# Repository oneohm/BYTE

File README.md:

# The BYTE
Full design package for the BYTE hands free interface

Details are available on the Hackaday project page:`
https://hackaday.io/project/171778-the-byte

## Repository Architecture

This repository is divided by 4 main folders:

- Docs: You'll find here our consult documents, and documentation of the project.
- Firmware: You'll find here everything you need to build the firmware and in case of needed, modify it.
- Hardware: You'll find here the KiCad projects with theirs libraries so the design is fully portable.
- Mechanical: You''ll find here all the FreeCad files to print/modify/understand the mechanics of the device.

You will find more information on each README in each folder, in order to keep this readme short.

# Previous Versions

It's important to note that this repository is under development, if your interested on one "The Byte" device already working, you should jump to the [Realese section](https://github.com/oneohm/BYTE/releases) of this repository to get the V1.0

## Version 1.0 

The version 1.0 has this architecture based on Seeeduino XIAO and all the connection is done by USB.

## License Info:

Firmware is licensed under the GNU General Public License v3.0

Hardware design is licensed under <br />This work is licensed under a <a rel="license" href="http://creativecommons.org/licenses/by-nc-sa/4.0/">Creative Commons Attribution-NonCommercial-ShareAlike 4.0 International License</a>.

Once the design is finalized the hardware will recieve a more permissive license.

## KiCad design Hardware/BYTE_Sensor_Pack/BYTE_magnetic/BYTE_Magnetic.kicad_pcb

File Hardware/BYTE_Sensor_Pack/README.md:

# The BYTE
Full design package for the BYTE hands free interface

Details are available on the Hackaday project page:`
https://hackaday.io/project/171778-the-byte

# Sensor Pack 

 You'll find here the KiCad projects for the different sensor packs.

- BYTE_Sensors.pretty: Library folder for all the KiCad footprints used in the sensor pack development.

- BYTE_FSR: First sensor pack used, only FSR for X/Y axis.

- BYTE_Bite: First sensor pack used, only FSR also for the bite.

- BYTE_Capacitive: Sensor intended to be used as capacitive feedback for FSR shift error.

- ...more to come.

## License Info:

Firmware is licensed under the GNU General Public License v3.0

Hardware design is licensed under <br />This work is licensed under a <a rel="license" href="http://creativecommons.org/licenses/by-nc-sa/4.0/">Creative Commons Attribution-NonCommercial-ShareAlike 4.0 International License</a>.

Once the design is finalized the hardware will recieve a more permissive license.

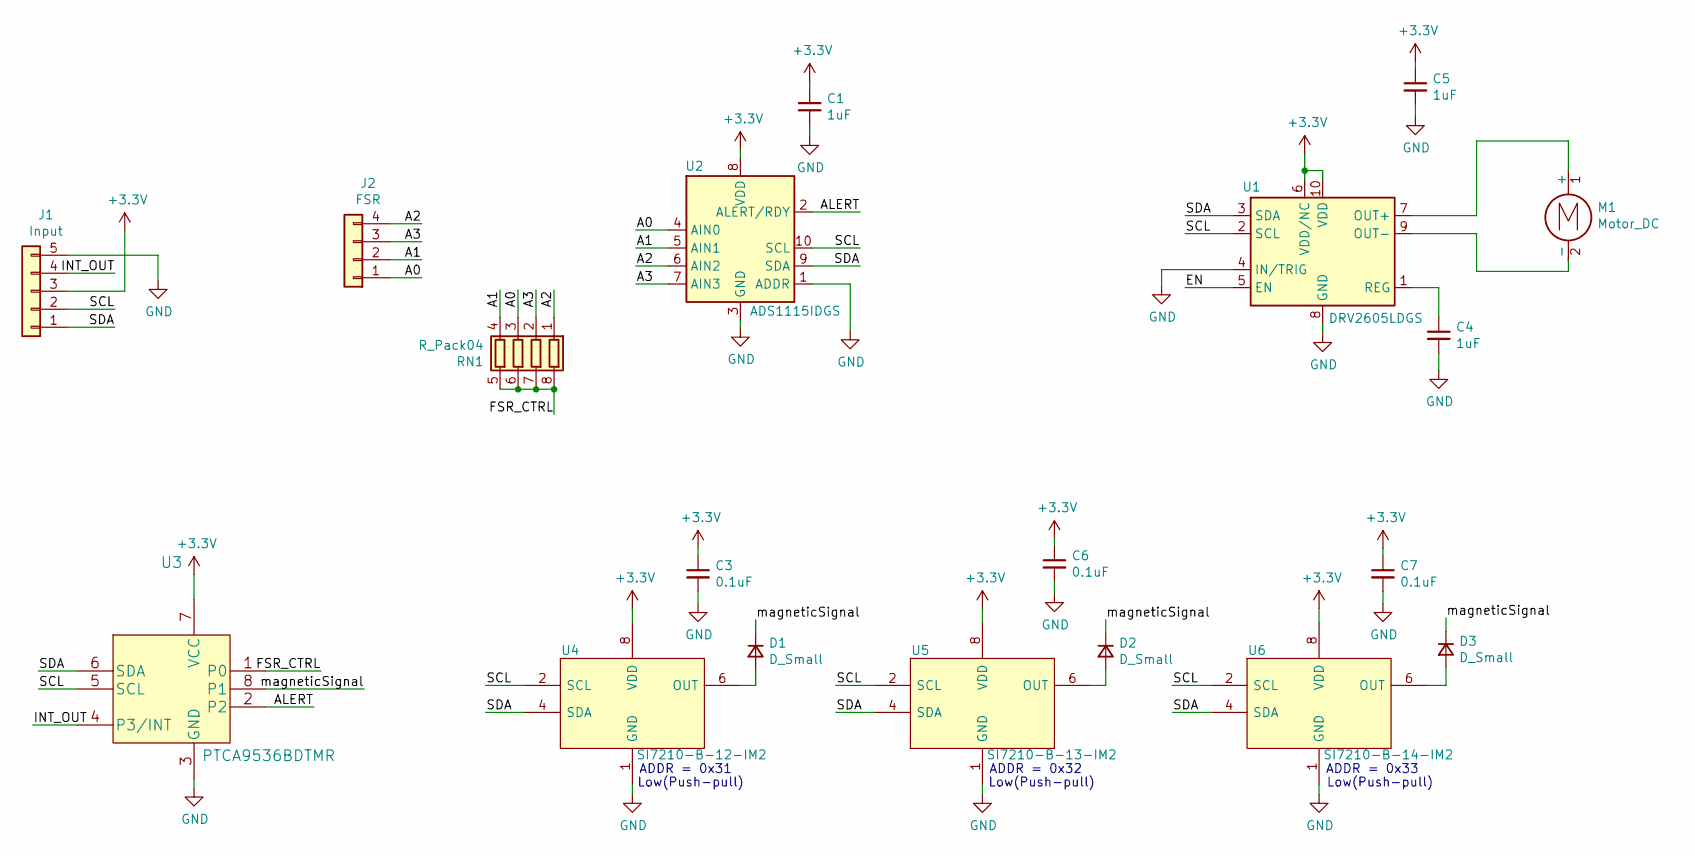
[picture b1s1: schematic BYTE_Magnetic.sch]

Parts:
C1, C4, C5: 1uF; C_0603_1608Metric
C3, C6, C7: 0.1uF; C_0603_1608Metric
D1, D2, D3: D_Small; D_0603_1608Metric
J1: Input; Flex_Connector
J2: FSR
M1: Motor_DC; VLV041235L
RN1: R_Pack04; R_Array_Convex_4x0603
U1: DRV2605LDGS; VSSOP-10_3x3mm_P0.5mm
U2: ADS1115IDGS; TSSOP-10_3x3mm_P0.5mm
U3: PTCA9536BDTMR; PTCA9416DTMR
U4: SI7210-B-12-IM2; SON40P140X160X40-8N-D
U5: SI7210-B-13-IM2; SON40P140X160X40-8N-D
U6: SI7210-B-14-IM2; SON40P140X160X40-8N-D

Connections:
+3V3: C1.1, C3.1, C5.1, C6.1, C7.1, J1.3, U1.6 (VDD/NC), U1.10 (VDD), U2.8 (VDD), U3.7 (VCC), U4.8 (VDD), U5.8 (VDD), U6.8 (VDD)
/A0: J2.1, RN1.3 (R3.1), U2.4 (AIN0)
/A1: J2.2, RN1.4 (R4.1), U2.5 (AIN1)
/A2: J2.4, RN1.1 (R1.1), U2.6 (AIN2)
/A3: J2.3, RN1.2 (R2.1), U2.7 (AIN3)
/ALERT: U2.2 (ALERT/RDY), U3.2
/EN: U1.5 (EN)
/FSR_CTRL: RN1.5 (R4.2), RN1.6 (R3.2), RN1.7 (R2.2), RN1.8 (R1.2), U3.1 (P0)
/INT_OUT: J1.4, U3.4 (P3/INT)
/SCL: J1.2, U1.2 (SCL), U2.10 (SCL), U3.5 (SCL), U4.2 (SCL), U5.2 (SCL), U6.2 (SCL)
/SDA: J1.1, U1.3 (SDA), U2.9 (SDA), U3.6 (SDA), U4.4 (SDA), U5.4 (SDA), U6.4 (SDA)
/magneticSignal: D1.1 (K), D2.1 (K), D3.1 (K), U3.8 (P1)
GND: C1.2, C3.2, C4.2, C5.2, C6.2, C7.2, J1.5, U1.4 (IN/TRIG), U1.8 (GND), U2.1 (ADDR), U2.3 (GND), U3.3 (GND), U4.1 (GND), U4.5 (GND), U5.1 (GND), U5.5 (GND), U6.1 (GND), U6.5 (GND)
unnamed: C4.1, U1.1 (REG)
unnamed: D1.2 (A), U4.6 (OUT)
unnamed: D2.2 (A), U5.6 (OUT)
unnamed: D3.2 (A), U6.6 (OUT)
unnamed: M1.1 (+), U1.7 (OUT+)
unnamed: M1.2 (-), U1.9 (OUT-)

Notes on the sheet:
ADDR = 0x31
ADDR = 0x32
ADDR = 0x33
Low(Push-pull)

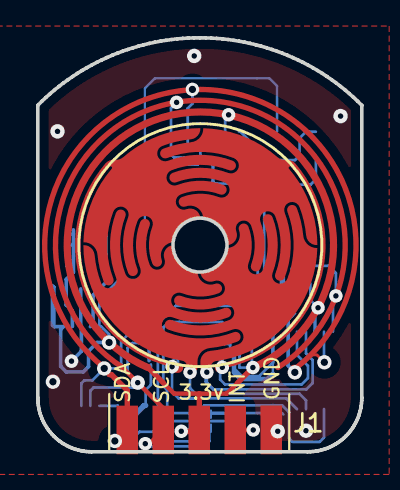
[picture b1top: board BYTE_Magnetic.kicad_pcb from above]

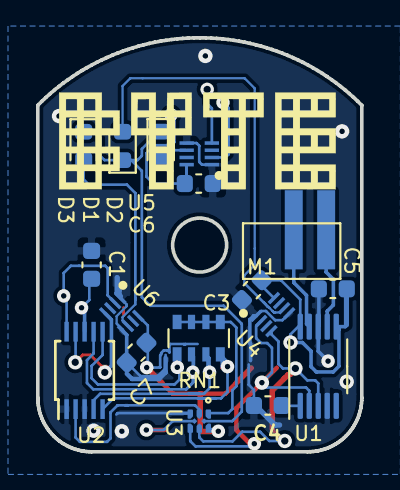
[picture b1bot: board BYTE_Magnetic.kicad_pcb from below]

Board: 2 copper layers, 18.0 x 23.0 mm, 19 parts (17 on the bottom side), 18 nets.

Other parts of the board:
Ref**: Val**; Logo

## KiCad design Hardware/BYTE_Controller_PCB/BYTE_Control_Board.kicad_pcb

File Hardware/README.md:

# The BYTE
Full design package for the BYTE hands free interface

Details are available on the Hackaday project page:`
https://hackaday.io/project/171778-the-byte

# Hardware 

 You'll find here the KiCad projects with theirs libraries so the design is fully portable among other folders with more hardware related information.

- BYTE_Bill_Of_Materials: Bill of materials of the electronics
- BYTE_Controller_PCB:  KiCad project for the main controller.
- BYTE_Full_Schematics: Full schematic in PDF for easy reading without KiCad.
- BYTE_Sensor_Artwork: All SVG files used to convert shapes from FreeCad to KiCad
- BYTE_Sensors_PCB: KiCad projects for the different sensor packs. 

You will find more information on each README in each folder, in order to keep this readme short.

## License Info:

Firmware is licensed under the GNU General Public License v3.0

Hardware design is licensed under <br />This work is licensed under a <a rel="license" href="http://creativecommons.org/licenses/by-nc-sa/4.0/">Creative Commons Attribution-NonCommercial-ShareAlike 4.0 International License</a>.

Once the design is finalized the hardware will recieve a more permissive license.

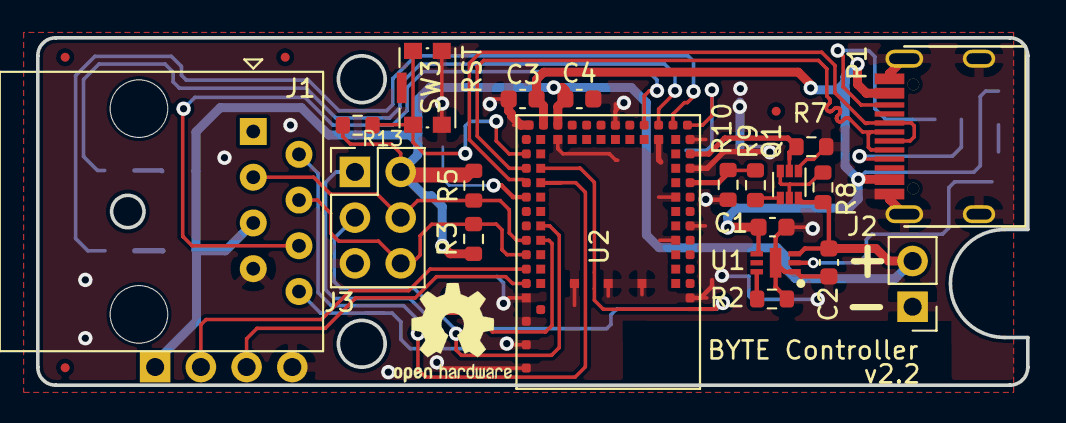
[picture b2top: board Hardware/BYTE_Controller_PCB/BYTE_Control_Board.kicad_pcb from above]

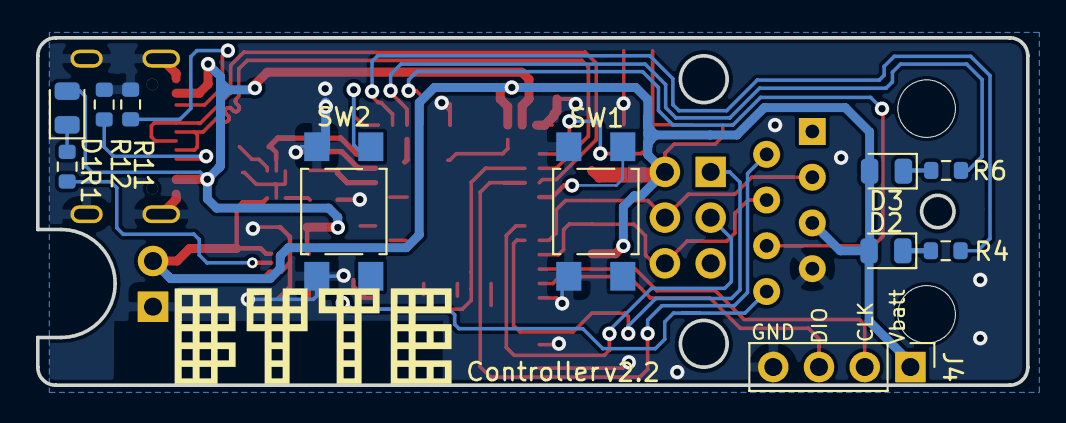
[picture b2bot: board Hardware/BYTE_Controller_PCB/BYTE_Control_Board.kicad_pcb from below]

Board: 2 copper layers, 55.0 x 19.3 mm, 32 parts (11 on the bottom side), 30 nets.

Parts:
C1, C2, C3: 4.7uF; C_0603_1608Metric
C4: 100nF; C_0603_1608Metric
D1, D2, D3: RED; LED_0805_2012Metric
J1: 8P8C_Shielded; RJ45_Amphenol_54602-x08_Horizontal
J2: Battery; PinHeader_1x02_P2.54mm_Vertical
J3: Expansion; PinHeader_2x03_P2.54mm_Vertical
J4: SWD; PinHeader_1x04_P2.54mm_Vertical
P1: USB_C_Plug_USB2.0; C393939
Q1: DMC2400UV; SOT-563
R1, R2, R3, R4, R5, R6, R7, R8, R9, R10: 2K; R_0603_1608Metric
R11: 5.1K; R_0603_1608Metric
R12: 5.1k; R_0603_1608Metric
R13: 10K; R_0603_1608Metric
Ref**: Val**; Logo
SW1, SW2: GPIO; SW_SPST_TL3305A
SW3: RST; SW_Push_1P1T-SH_NO_CK_KMR2xxG
U1: MCP73830T-2AAI_MYY; 2x2TDFN
U2: BL653; BL653_v5

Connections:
+BATT: C2.1, C4.1, D2.2, D3.2, J1.5, J2.2, J3.2, J4.1, Q1.6, R3.2, R5.2, R8.2, R13.2, U1.3, U2.25
/BATT_LVL: R9.1, R10.2, U2.49
/BATT_LVL_EN: Q1.2, R7.2, U2.45
/BYTE_SENSOR_1: J1.2, U2.16
/BYTE_SENSOR_2: J1.8, U2.18
/CC1: P1.A5, R12.1
/CC2: P1.B5, R11.2
/D+: P1.A6, U2.15
/D-: P1.A7, U2.17
/RST: R13.1, SW3.1, U2.19
/SCL: J1.4, J3.6, R3.1, U2.5
/SDA: J1.3, J3.4, R5.1, U2.7
/SIO_0: SW2.1, U2.42
/SIO_1: R4.1, U2.41
/SIO_5: R6.1, U2.39
/SIO_20: SW1.1, U2.13
/SIO_24: J3.3, U2.10
/SIO_25: J3.1, U2.8
/STAT: R1.1, U1.2
/SWCLK: J4.2, U2.3
/SWDIO: J4.3, U2.1
/Sensor_INT: J1.6, U2.37
GND: C1.2, C2.2, C3.2, C4.2, J1.7, J2.1, J3.5, J4.4, P1.A1, P1.S1, Q1.1, R2.1, R7.1, R10.1, R11.1, R12.2, SW1.2, SW2.2, SW3.2, U1.1, U1.7, U2.0, U2.23, U2.26, U2.33, U2.40, U2.43, U2.47, U2.52, U2.55, U2.58, U2.65, U2.66, U2.67, U2.68, U2.69, U2.70, U2.71
unnamed: D1.1, R1.2
unnamed: D2.1, R4.2
unnamed: D3.1, R6.2
unnamed: Q1.3, Q1.5, R8.1
unnamed: Q1.4, R9.2
unnamed: R2.2, U1.6
VBUS: C1.1, C3.1, D1.2, P1.A4, U1.4, U2.24

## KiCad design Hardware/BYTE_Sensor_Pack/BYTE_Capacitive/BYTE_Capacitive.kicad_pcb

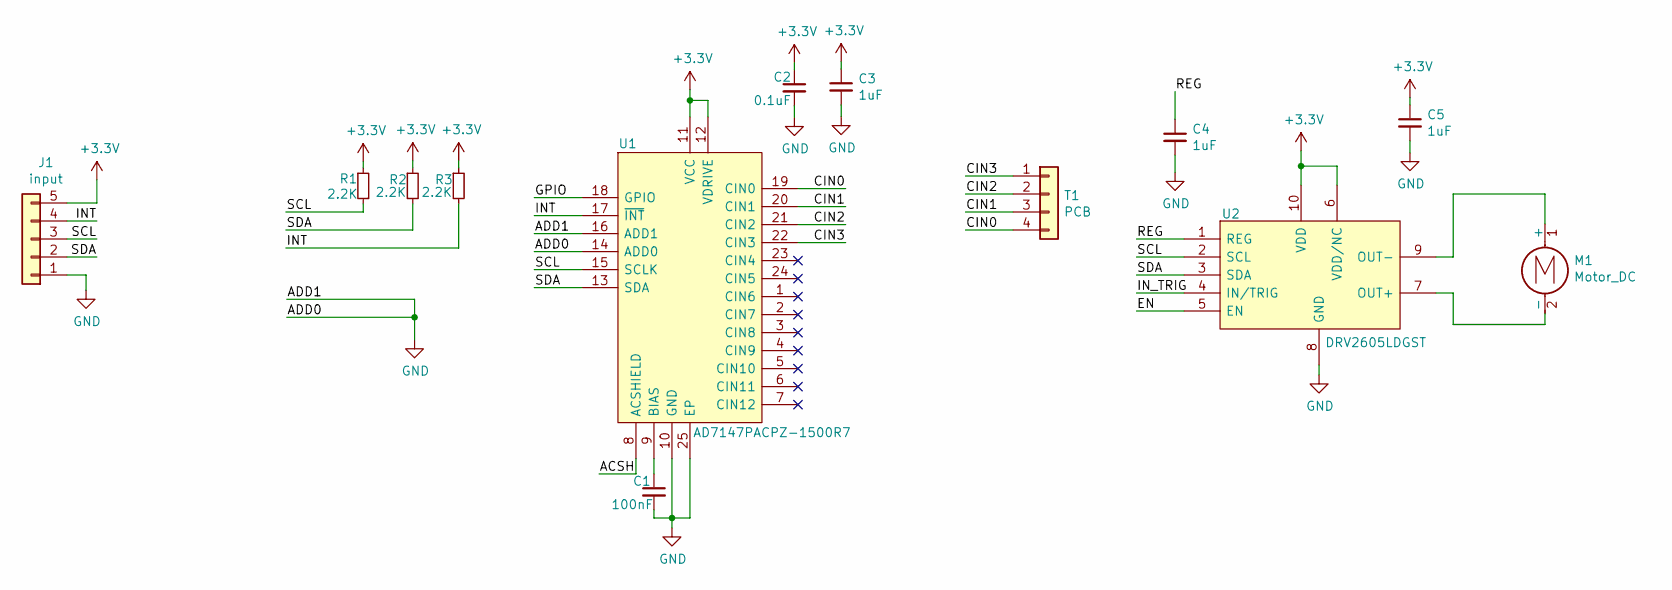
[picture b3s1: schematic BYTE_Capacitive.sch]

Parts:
C1: 100nF; C_0402_1005Metric
C2: 0.1uF; C_0402_1005Metric
C3, C4, C5: 1uF; C_0402_1005Metric
J1: input; Flex_Connector
M1: Motor_DC; VLV041235L
R1, R2, R3: 2.2K; R_0402_1005Metric
T1: PCB; Capacitive_PCB_NoConnector
U1: AD7147PACPZ-1500R7; QFN50P400X400X80-25N-D
U2: DRV2605LDGST; SOP50P490X110-10N

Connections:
+3V3: C2.1, C3.1, C5.1, J1.5, R1.1, R2.1, R3.1, U1.11 (VCC), U1.12 (VDRIVE), U2.6 (VDD/NC), U2.10 (VDD)
/ACSH: U1.8 (ACSHIELD)
/CIN0: T1.4, U1.19 (CIN0)
/CIN1: T1.3, U1.20 (CIN1)
/CIN2: T1.2, U1.21 (CIN2)
/CIN3: T1.1, U1.22 (CIN3)
/EN: U2.5 (EN)
/GPIO: U1.18 (GPIO)
/INT: J1.4, R3.2, U1.17 (~INT)
/IN_TRIG: U2.4 (IN/TRIG)
/REG: C4.1, U2.1 (REG)
/SCL: J1.3, R1.2, U1.15 (SCLK), U2.2 (SCL)
/SDA: J1.2, R2.2, U1.13 (SDA), U2.3 (SDA)
GND: C1.2, C2.2, C3.2, C4.2, C5.2, J1.1, U1.10 (GND), U1.14 (ADD0), U1.16 (ADD1), U1.25 (EP), U2.8 (GND)
unnamed: C1.1, U1.9 (BIAS)
unnamed: M1.1 (+), U2.9 (OUT-)
unnamed: M1.2 (-), U2.7 (OUT+)

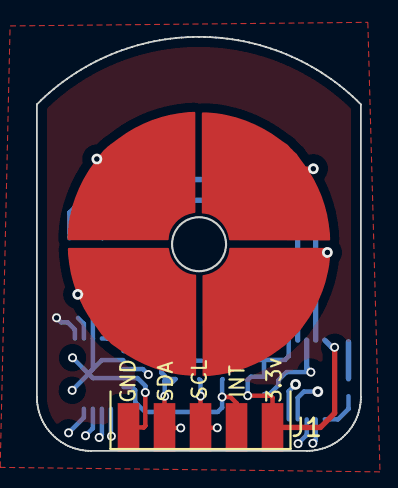
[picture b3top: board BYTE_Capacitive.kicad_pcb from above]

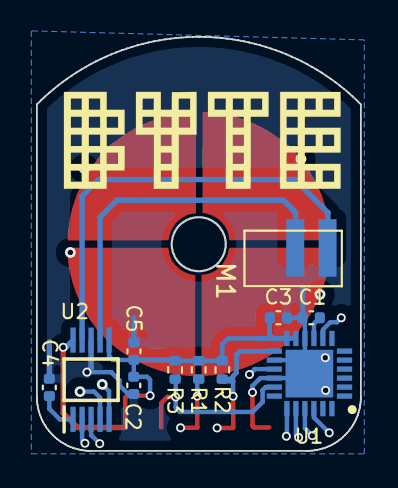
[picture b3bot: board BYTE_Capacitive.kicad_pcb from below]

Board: 4 copper layers, 18.0 x 23.0 mm, 14 parts (11 on the bottom side), 13 nets.

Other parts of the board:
Ref**: Val**; Logo

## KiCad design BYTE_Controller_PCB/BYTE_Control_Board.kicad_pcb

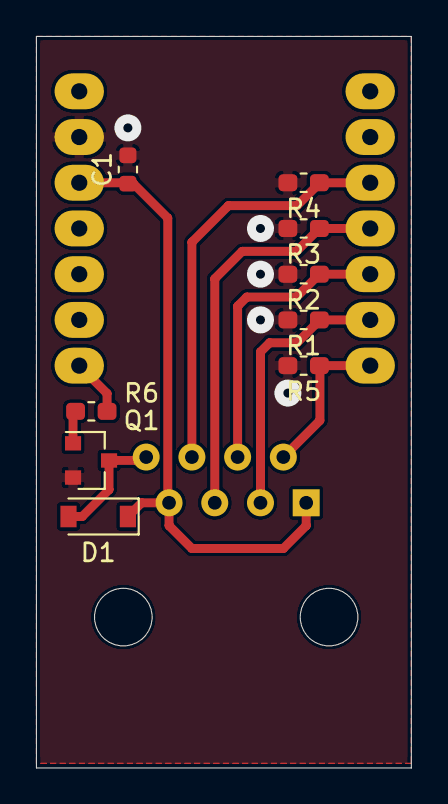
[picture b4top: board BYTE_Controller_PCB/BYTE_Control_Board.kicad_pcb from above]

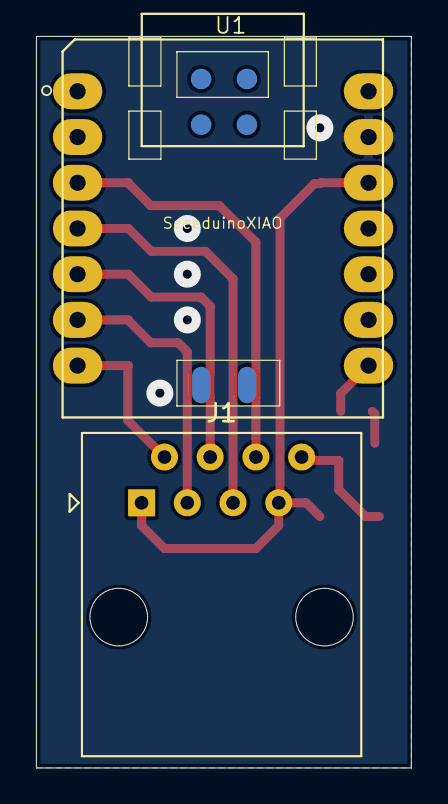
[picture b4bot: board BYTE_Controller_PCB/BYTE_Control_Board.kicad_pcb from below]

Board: 2 copper layers, 20.8 x 40.6 mm, 11 parts (2 on the bottom side), 10 nets.

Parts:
C1: C; C_0603_1608Metric
D1: D_Schottky; D_SOD-123
J1: 8P8C_Shielded; RJ45_Amphenol_54602-x08_Horizontal
Q1: 2N7002; SOT-23
R1, R2, R3, R4, R5, R6: R_US; R_0603_1608Metric_Pad1.05x0.95mm_HandSolder
U1: SeeeduinoXIAO; XIAO-MOUDLE14P-2.54-21X17.8MM_Through_Hole

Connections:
GND: C1.2, Q1.2, R1.2, R2.2, R3.2, R4.2, R5.2, U1.13
unnamed: C1.1, D1.1, J1.1, J1.7, U1.12
unnamed: D1.2, J1.8, Q1.3
unnamed: J1.2, R5.1, U1.7
unnamed: J1.3, R1.1, U1.6
unnamed: J1.4, R2.1, U1.5
unnamed: J1.5, R3.1, U1.4
unnamed: J1.6, R4.1, U1.3
unnamed: Q1.1, R6.2
unnamed: R6.1, U1.8

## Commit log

2020-08-31 Initial Upload
2020-09-10 Including printable part models
2020-09-11 Including Enclosure Design
2020-09-11 Including Bill of Materials
2020-09-11 renamed BOM PDF
2020-09-22 Adding Schematics and Block Diagram
2020-10-05 Adding Testing Procedure
2020-10-05 Create LICENSE
    Adding license for the firmware
2020-10-05 Update BYTE_Firmware_19.ino
    Adding License info
2021-08-13 erase .DS_Store
2021-08-13 Add Docs folder
2021-08-13 add firmware folder
2021-08-13 add hardware folder
2021-08-13 add mechanical folder
2021-08-13 add more .ds_store to gitignore
2021-08-18 PCB Manufacturing Artwork
    These SVG files contain the geometry required for the sensor pack PCBs
2021-08-18 Sensor PBC artwork
    Re-arranging the folder structure
2021-08-23 Add sensor pack folder for different sensors KiCad projects
2021-08-23 add project list
2021-08-23 add assets
2021-08-23 add READMEs
2021-08-24 add magnetic sensor test firmware with arduino
2021-08-30 modify footprints
2021-08-30 add projects
2021-08-30 update readme, fiz gitignore, for backup files from kicad
2021-08-30 fix name asset
2021-09-06 update capacitive ICs
2021-09-06 add magnetic sensing
2021-09-06 update sch magnetic
2021-09-08 modify library for ldr controller
2021-09-08 update capacitive sensor board
2021-09-08 update magnetic layout
2021-09-13 modify magnetic
2021-09-15 add footprint for FSR and LRA motor
2021-09-15 update magnetic sensor, merge with FSR
2021-09-15 add motor footprint
2021-09-21 modify controller board
2021-09-22 update pcbs
2021-09-22 update gnd route
2021-09-23 update magentic adding I2C I/O controller
2021-09-23 update controller PCB added battery reading circuit
2021-09-24 update magnetic sensor
2021-09-24 update 3D models
2021-09-28 update magnetic pcb and
2021-09-30 update byte controller
2021-09-30 upload cache
2021-10-02 move ICs 0.5 to center, magnetic sensor
2021-10-04 update byte controller for hand made
2021-10-05 add byte panel for manufacture
2021-10-07 prepare for manufacture
2021-10-07 modify gerbers
2021-10-11 add manufacturer part number for BOM
